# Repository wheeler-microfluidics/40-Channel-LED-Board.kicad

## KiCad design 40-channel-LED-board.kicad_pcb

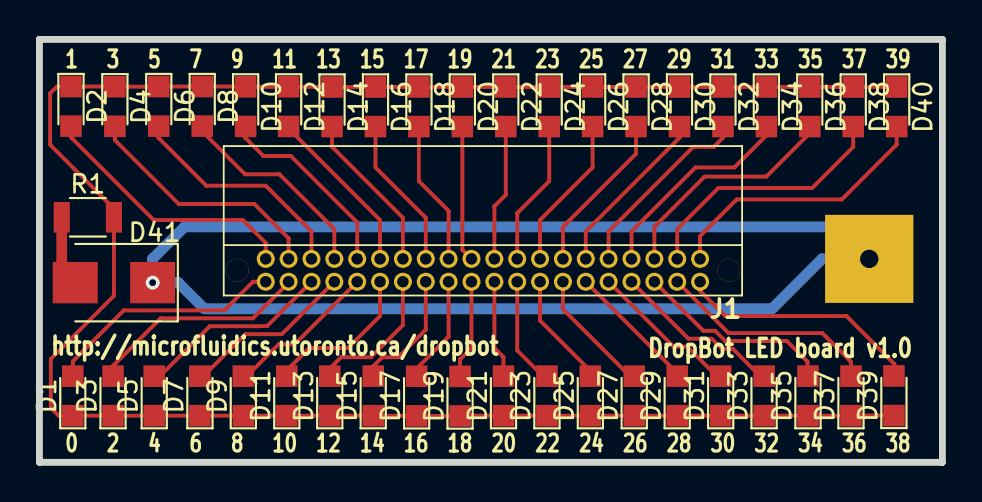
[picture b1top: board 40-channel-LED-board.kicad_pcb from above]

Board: 2 copper layers, 50.2 x 23.5 mm, 44 parts (0 on the bottom side), 43 nets.

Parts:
D1, D2, D3, D4, D5, D6, D7, D8, D9, D10, D11, D12, D13, D14, D15, D16, D17, D18, D19, D20, D21, D22, D23, D24, D25, D26, D27, D28, D29, D30, D31, D32, D33, D34, D35, D36, D37, D38, D39, D40: LED; LED_0805
D41: D_Zener; D_SMB
J1: CONN_40; TFML-120-01-XXX-D-RA
P1: CONN_01X01; 4.9mm_DMF_Electrode
R1: R; R_1206

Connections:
unnamed: D1.1, D2.1, D3.1, D4.1, D5.1, D6.1, D7.1, D8.1, D9.1, D10.1, D11.1, D12.1, D13.1, D14.1, D15.1, D16.1, D17.1, D18.1, D19.1, D20.1, D21.1, D22.1, D23.1, D24.1, D25.1, D26.1, D27.1, D28.1, D29.1, D30.1, D31.1, D32.1, D33.1, D34.1, D35.1, D36.1, D37.1, D38.1, D39.1, D40.1, R1.2
unnamed: D1.2, J1.1
unnamed: D2.2, J1.2
unnamed: D3.2, J1.3
unnamed: D4.2, J1.4
unnamed: D5.2, J1.5
unnamed: D6.2, J1.6
unnamed: D7.2, J1.7
unnamed: D8.2, J1.8
unnamed: D9.2, J1.9
unnamed: D10.2, J1.10
unnamed: D11.2, J1.11
unnamed: D12.2, J1.12
unnamed: D13.2, J1.13
unnamed: D14.2, J1.14
unnamed: D15.2, J1.15
unnamed: D16.2, J1.16
unnamed: D17.2, J1.17
unnamed: D18.2, J1.18
unnamed: D19.2, J1.19
unnamed: D20.2, J1.20
unnamed: D21.2, J1.21
unnamed: D22.2, J1.22
unnamed: D23.2, J1.23
unnamed: D24.2, J1.24
unnamed: D25.2, J1.25
unnamed: D26.2, J1.26
unnamed: D27.2, J1.27
unnamed: D28.2, J1.28
unnamed: D29.2, J1.29
unnamed: D30.2, J1.30
unnamed: D31.2, J1.31
unnamed: D32.2, J1.32
unnamed: D33.2, J1.33
unnamed: D34.2, J1.34
unnamed: D35.2, J1.35
unnamed: D36.2, J1.36
unnamed: D37.2, J1.37
unnamed: D38.2, J1.38
unnamed: D39.2, J1.39
unnamed: D40.2, J1.40
unnamed: D41.1, P1.1
unnamed: D41.2, R1.1

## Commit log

2018-05-22 Change trace width
2018-05-22 Removed 'special' library
